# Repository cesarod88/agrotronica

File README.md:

# Agrotronics Integrated Ecosystem 🌿📡

Este repositorio contiene la arquitectura técnica, firmware y modelos de análisis para un ecosistema agrotrónico modular. El sistema gestiona tres cultivos específicos (Café, Lechuga, Tomate) mediante una red híbrida de sensores y actuadores.

---

## 🏗️ Arquitectura del Sistema

### 1. Nodo Café (Riego por Dispersión)
* **Control:** PCB personalizada con regulador **$7805$** y filtrado robusto.
* **Infraestructura:** Conectividad mediante **UTP/RJ45** para el transporte de señales de 4 sensores de humedad y activación de electroválvula de 12V.
* **Energía:** Sistema fotovoltaico de 50W, batería de 2000mAh y regulador de 12V.

### 2. Nodo Hidráulico & Lechuga (Gravedad y Monitoreo Distribuidos)
Este nodo gestiona el riego por gravedad (Goteo/Chorro) y el monitoreo de precisión en eras de lechuga.
* **Control de Riego:** Heltec WiFi LoRa 32 V3 que monitorea un transductor de presión ($0.5V - 4.5V$, $1.6 \text{ MPa}$) y activa un relé de 5V.
* **Red de Sensores (Cultivo de Lechuga):** * 6 Sensores **Makerfabs LoRaWAN** (Humedad de Suelo y Temperatura).
    * Distribución en **2 eras** de cultivo.
    * Autonomía: Baterías AAA con reporte cada 60 minutos.
* **Flujo de Datos:** * Sensores -> TTN (The Things Network) -> Google Sheets (Consulta pública).
    * **Redundancia:** El Heltec conmuta entre WiFi (directo a Sheets) y LoRa (vía TTN) según disponibilidad.

### 3. Nodo Tomate (Edge IA & Potencia)
* **Cerebro:** Raspberry Pi 4 con cámara integrada.
* **Potencia:** Activación de bomba de $127VAC$ con protección termomagnética de $50A$.
* **Interconexión:** Gateway para estación **Libelium Plug & Sense** (Viento y Lluvia) vía LoRa.
* **IA:** Análisis de imágenes para la salud del cultivo de tomate.

---

## 📊 Visualización Avanzada (Dashboard)

El sistema centraliza los datos en una aplicación interactiva con las siguientes capacidades:

* **Mapa de Calor (Heat Map):** Generación en tiempo real de la distribución de humedad en el cultivo de lechuga basado en los 6 nodos Makerfabs. Permite identificar zonas de estrés hídrico o sobre-riego.
* **Gestión Individual y Global:** Control manual de electroválvulas y bombas, además de modos automáticos basados en umbrales.
* **Roles y Expertos:** Sistema de permisos para operarios, agrónomos y administradores de red.

---

## 🔒 Seguridad y Certificaciones

| Capa | Implementación |
| :--- | :--- |
| **Ciberseguridad** | Encriptación **AES-128** en capas de red LoRaWAN y **TLS 1.3** para tráfico Web/WiFi. |
| **Hardware** | Diseño de PCBs bajo normas **IPC-2221**; cableado UTP con blindaje para reducir ruido en señales analógicas. |
| **Cómputo** | Procesamiento en el borde (Edge) en RPI4 para reducir latencia en la IA de visión. |

---

## 📂 Estructura del Repositorio

```text
├── /hardware           # Esquemáticos (PCBs, Sensores Makerfabs, Conexiones RJ45)
├── /firmware           # Código para Heltec, ESP32 y RPI4
├── /cloud_integration  # Google Apps Scripts y Webhooks para TTN
├── /dashboard          # App frontend (Visualización de Heat Maps y telemetría)
└── /ai_vision          # Modelos de detección para el Nodo Tomate

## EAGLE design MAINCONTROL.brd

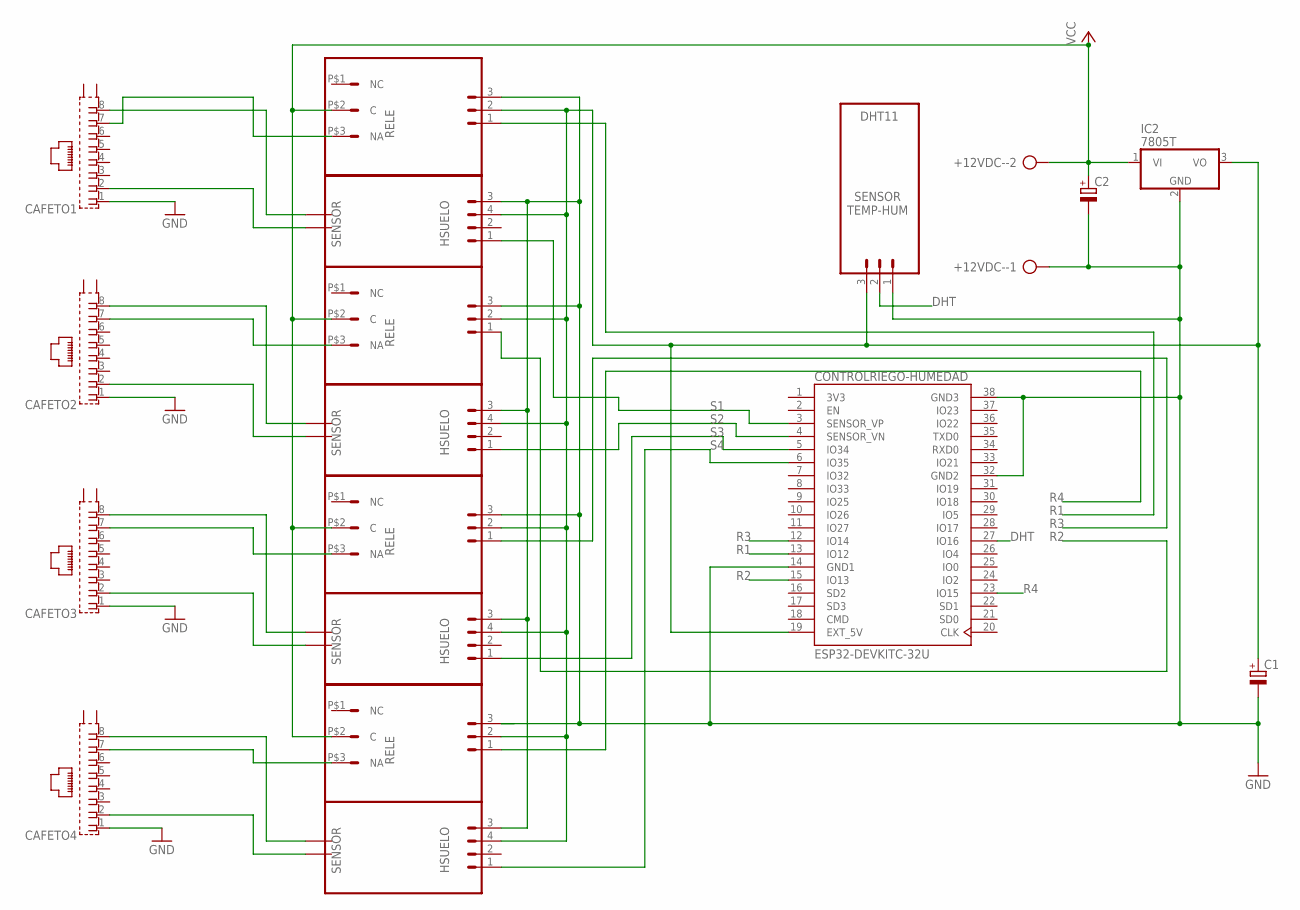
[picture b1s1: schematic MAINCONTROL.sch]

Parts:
+12VDC-: AK500/2-H
C1: CPOL-EUE2.5-6; E2,5-6
C2: CPOL-EUE2,5-6E; E2,5-6E
CAFETO1, CAFETO2, CAFETO3, CAFETO4: RJ45-8N3-B; TE_RJ45-8N3-B
CONTROLRIEGO-HUMEDAD: ESP32-DEVKITC-32U; MODULE_ESP32-DEVKITC-32U
IC2: 7805T; TO220H
SV1, SV5, SV6, SV7: RELE; MA03-1
SV2: DHT11
SV3, SV4, SV8, SV9: HSUELO

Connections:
3V3: CONTROLRIEGO-HUMEDAD.1 (3V3)
DHT: CONTROLRIEGO-HUMEDAD.27 (IO16), SV2.2
GND: +12VDC-.1, C1.-, C2.-, CAFETO1.1, CAFETO2.1, CAFETO3.1, CAFETO4.1, CONTROLRIEGO-HUMEDAD.14 (GND1), CONTROLRIEGO-HUMEDAD.32 (GND2), CONTROLRIEGO-HUMEDAD.38 (GND3), IC2.2 (GND), SV1.3 (GND), SV2.1 (3), SV3.3 (4), SV4.3 (4), SV5.3 (GND), SV6.3 (GND), SV7.3 (GND), SV8.3 (4), SV9.3 (4)
unnamed: CAFETO1.2, SV8.S2 (6)
unnamed: CAFETO1.7, SV1.P$3 (NA)
unnamed: CAFETO2.7, SV5.P$3 (NA)
unnamed: CAFETO1.8, SV8.S1 (5)
unnamed: CAFETO2.8, SV4.S1 (5)
unnamed: CAFETO2.2, SV4.S2 (6)
unnamed: CAFETO3.8, SV3.S1 (5)
unnamed: CAFETO3.2, SV3.S2 (6)
unnamed: CAFETO4.7, SV7.P$3 (NA)
unnamed: CAFETO3.7, SV6.P$3 (NA)
unnamed: CAFETO4.8, SV9.S1 (5)
unnamed: CAFETO4.2, SV9.S2 (6)
R1: CONTROLRIEGO-HUMEDAD.13 (IO12), SV1.1 (S)
R2: CONTROLRIEGO-HUMEDAD.15 (IO13), SV5.1 (S)
R3: CONTROLRIEGO-HUMEDAD.12 (IO14), SV6.1 (S)
R4: CONTROLRIEGO-HUMEDAD.23 (IO15), SV7.1 (S)
S1: CONTROLRIEGO-HUMEDAD.3 (SENSOR_VP), SV8.1
S2: CONTROLRIEGO-HUMEDAD.4 (SENSOR_VN), SV4.1
S3: CONTROLRIEGO-HUMEDAD.5 (IO34), SV3.1
S4: CONTROLRIEGO-HUMEDAD.6 (IO35), SV9.1
VCC: +12VDC-.2, C2.+, IC2.1 (VI), SV1.P$2 (C), SV5.P$2 (C), SV6.P$2 (C), SV7.P$2 (C)
VO: C1.+, CONTROLRIEGO-HUMEDAD.19 (EXT_5V), IC2.3 (VO), SV1.2 (VCC), SV2.3 (1), SV3.4 (3), SV4.4 (3), SV5.2 (VCC), SV6.2 (VCC), SV7.2 (VCC), SV8.4 (3), SV9.4 (3)

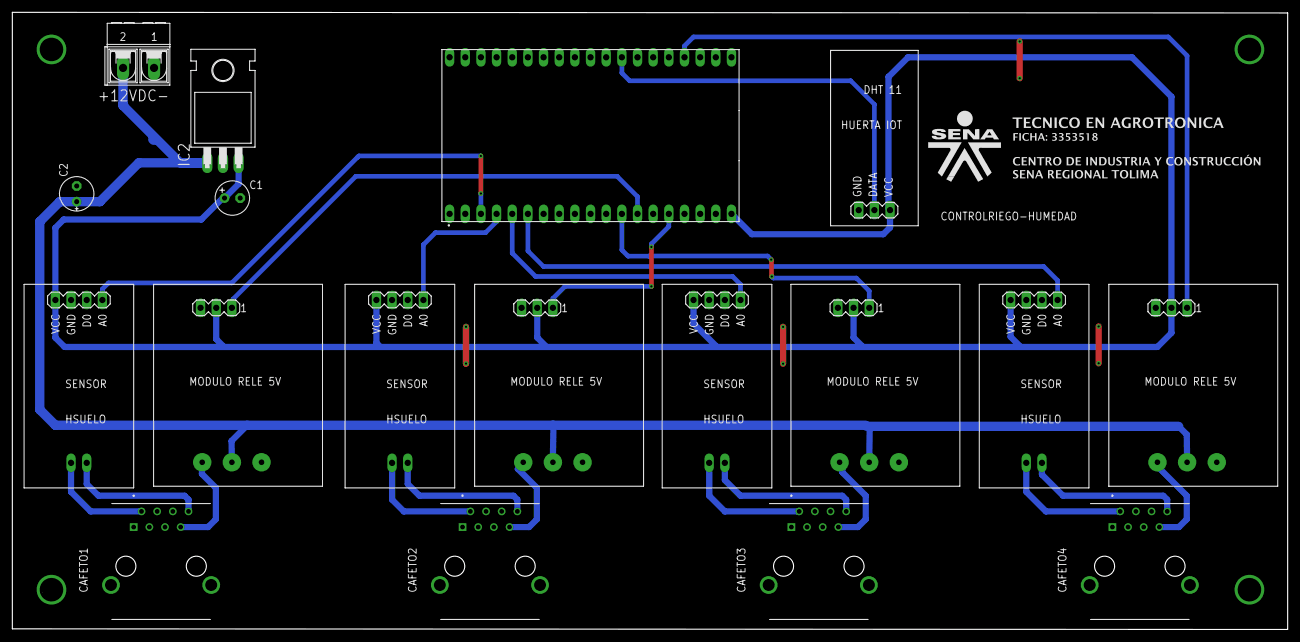
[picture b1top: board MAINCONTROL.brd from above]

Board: 2 copper layers, 206.9 x 100.1 mm, 18 parts (0 on the bottom side), 24 nets.

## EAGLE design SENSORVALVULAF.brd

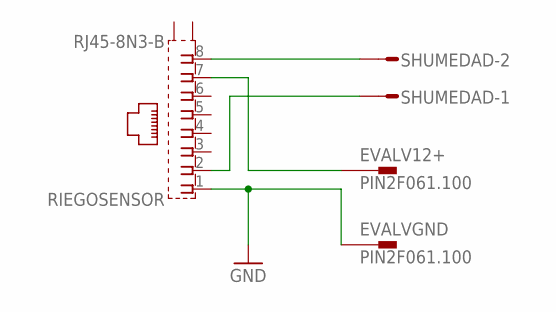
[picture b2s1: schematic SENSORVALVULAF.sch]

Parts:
EVALV12+: PIN2F061.100; F061.100
EVALVGND: PIN2F061.100; F061.100
RIEGOSENSOR: RJ45-8N3-B; TE_RJ45-8N3-B
SHUMEDAD: L02P

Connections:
GND: EVALVGND.A1, EVALVGND.A2, RIEGOSENSOR.1
unnamed: RIEGOSENSOR.8, SHUMEDAD.2
unnamed: RIEGOSENSOR.2, SHUMEDAD.1
unnamed: EVALV12+.A1, EVALV12+.A2, RIEGOSENSOR.7

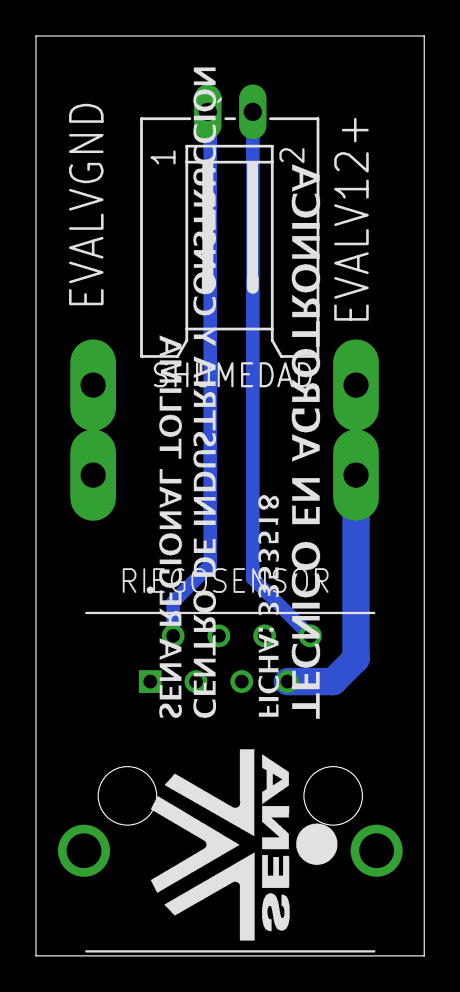
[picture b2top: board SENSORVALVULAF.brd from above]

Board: 2 copper layers, 21.6 x 51.1 mm, 4 parts (1 on the bottom side), 4 nets.

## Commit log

2026-04-22 Revise README for Agrotronics project documentation
    Updated the README to provide detailed project documentation, including system architecture, security standards, repository structure, and quick installation guide.
2026-04-22 Revise README with updated project details and nodes
    Updated project description, added new nodes, and improved security details.
2026-04-24 Delete MAINCONTROL.brd
    Actualizacion de ESP
2026-04-24 Delete MAINCONTROL.sch
    Actualizacion ESP
2026-04-24 Add files via upload
    Cambio de ESP por ESP con antena.

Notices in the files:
README.md:
License: MIT
